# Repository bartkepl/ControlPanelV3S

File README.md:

# ControlPanelV3S — Hardware

KiCad project for the CAN-bus control panel board built around the Allwinner V3S (LicheePi Zero),
part of the [CANbusSensors](../) family of MPCC/MPSWP sensor-node projects. Two assembly variants
on one PCB: a handheld CAN-bus terminal and a VoIP endpoint. The next hardware iteration (Allwinner
T113-S3/4) will be a separate repo.

## Status: ready for prototype order

- Schematic and PCB layout done (4-layer, 120 × 75 mm), production files generated.
- Design review completed; DRC/ERC clean (remaining items reviewed and excluded as by-design).
- Hand assembly (2 fiducials on F.Cu for stencil alignment); crystal load caps C3/C4 are placeholders to be tuned at bring-up.

Production outputs: [schematic PDF](prod/sch/ControlPanel.pdf) · [PCB PDF](prod/pcb/ControlPanel.pdf) · [interactive BOM](prod/ibom/ControlPanel_ibom.html) · [gerbers](prod/ControlPanelV3S.zip)

## Renders

3D renders straight out of KiCad (`pcb/gen_media.kicad_jobset`), not photos — no boards have been
fabricated yet.

| Top | Bottom | Angle |
|---|---|---|
|  |  |  |

## Layout

- **`pcb/`** - KiCad project: CPU, power, CAN transceiver front-end, display/touch, GPS, Ethernet,
  audio.
- **`doc/`** - hardware design decisions and reference material. Start with
  [doc/README.md](doc/README.md), which says which document is the source of truth for what.
- **`media/`** - 3D renders of the board, generated from the KiCad project.
- **`prod/`** - fabrication outputs (gerber + drill zip, BOM, interactive BOM, schematic/PCB PDFs).

## Firmware

The firmware that runs on this board (V3S-side kiosk app, CAN-bus device monitor, offline
navigation/map stack) lives in a separate, currently private companion repo.

## License

MIT for original work - see [LICENSE](LICENSE). All footprints live under `pcb/local_lib/` and
were either authored locally or sourced from SamacSys (`BAT_MS621FE-FL11E.kicad_mod`); 
FunKey S is referenced in `doc/` as a comparison point for the Allwinner V3S reference design 
(e.g. power-tree, boot ROM behavior).

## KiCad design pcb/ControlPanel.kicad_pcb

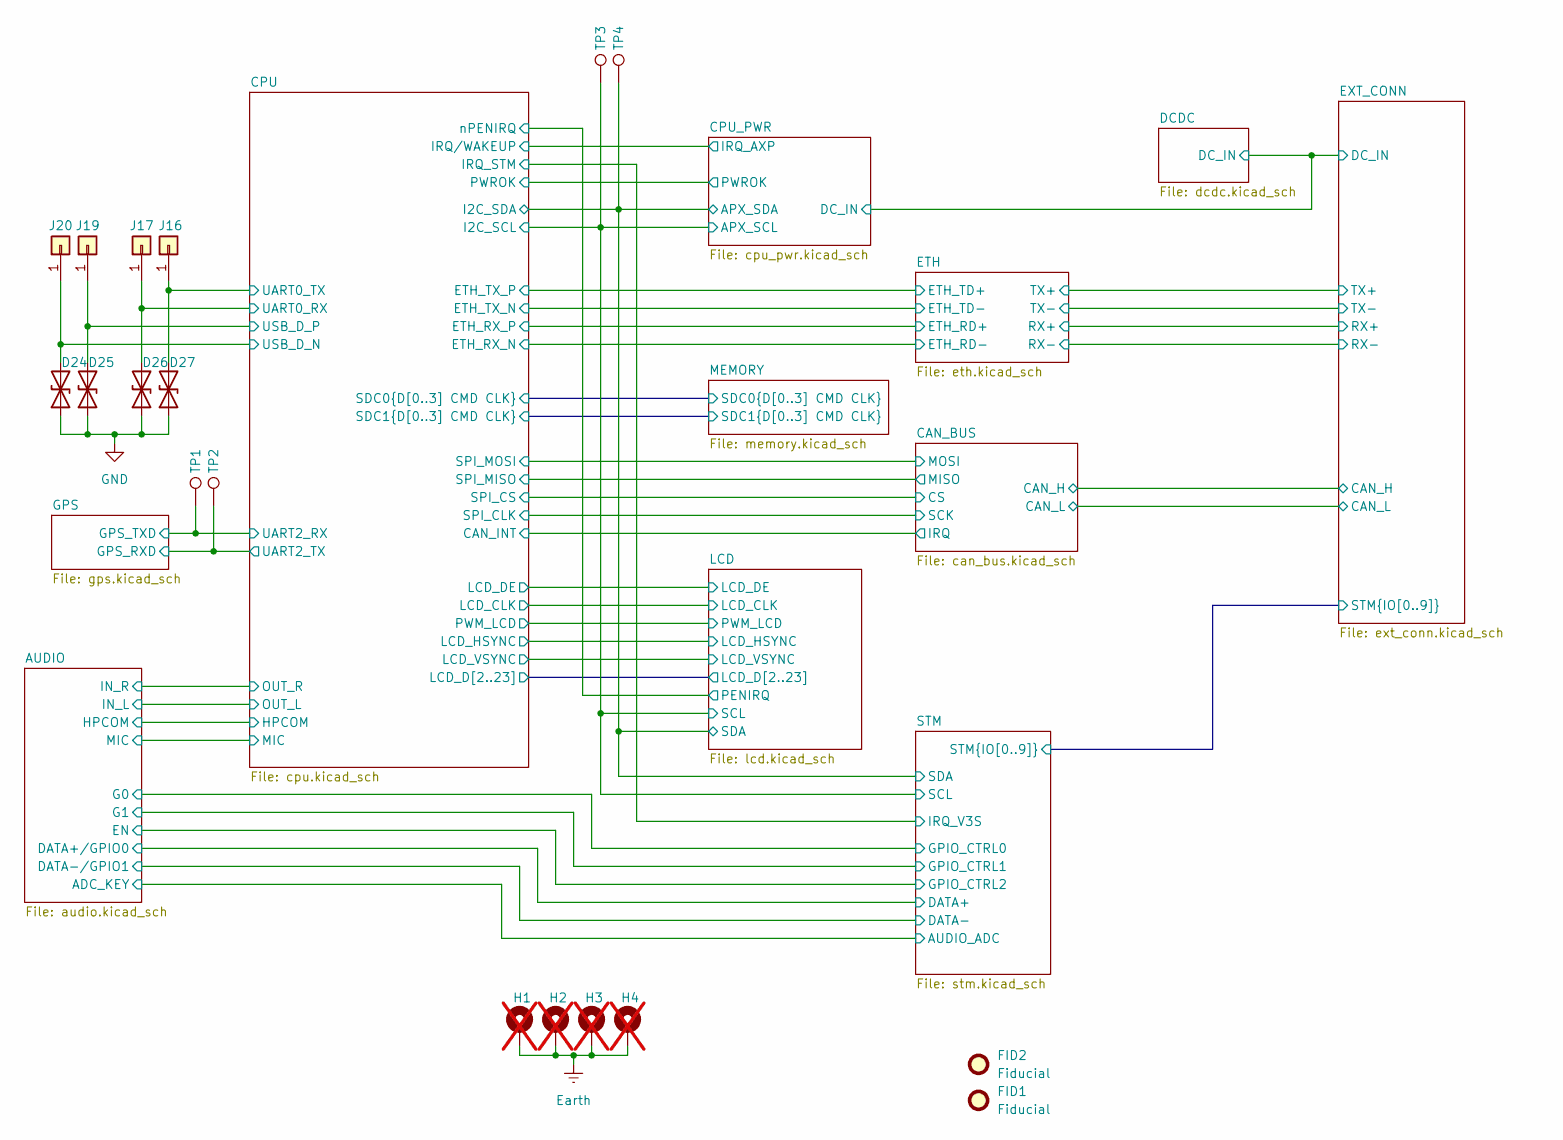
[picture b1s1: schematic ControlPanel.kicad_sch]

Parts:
D24, D25, D26, D27: STN061050BL40; D_0603_1608Metric; MPN STN061050BL40
FID1, FID2: Fiducial; Fiducial_0.5mm_Mask1mm
H1, H2, H3, H4: MountingHole_Pad; MountingHole_3.2mm_M3_ISO14580_Pad_TopBottom; not fitted
J16, J17, J19, J20: Conn_01x01; TestPoint_Pad_1.0x1.0mm
TP1, TP2, TP3, TP4: TestPoint; TestPoint_Pad_D1.0mm

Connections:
/CPU/I2C_SCL: TP3.1 (1_1); also elsewhere on the board
/CPU/I2C_SDA: TP4.1 (1_1); also elsewhere on the board
/CPU/UART0_RX: D26.2 (A2), J17.1 (Pin_1_1); also elsewhere on the board
/CPU/UART0_TX: D27.2 (A2), J16.1 (Pin_1_1); also elsewhere on the board
/CPU/UART2_RX: TP1.1 (1_1); also elsewhere on the board
/CPU/UART2_TX: TP2.1 (1_1); also elsewhere on the board
/CPU/USB_D_N: D24.2 (A2), J20.1 (Pin_1_1); also elsewhere on the board
/CPU/USB_D_P: D25.2 (A2), J19.1 (Pin_1_1); also elsewhere on the board
Earth: H1.1 (1_1), H2.1 (1_1), H3.1 (1_1), H4.1 (1_1); also elsewhere on the board
GND: D24.1 (A1), D25.1 (A1), D26.1 (A1), D27.1 (A1); also elsewhere on the board

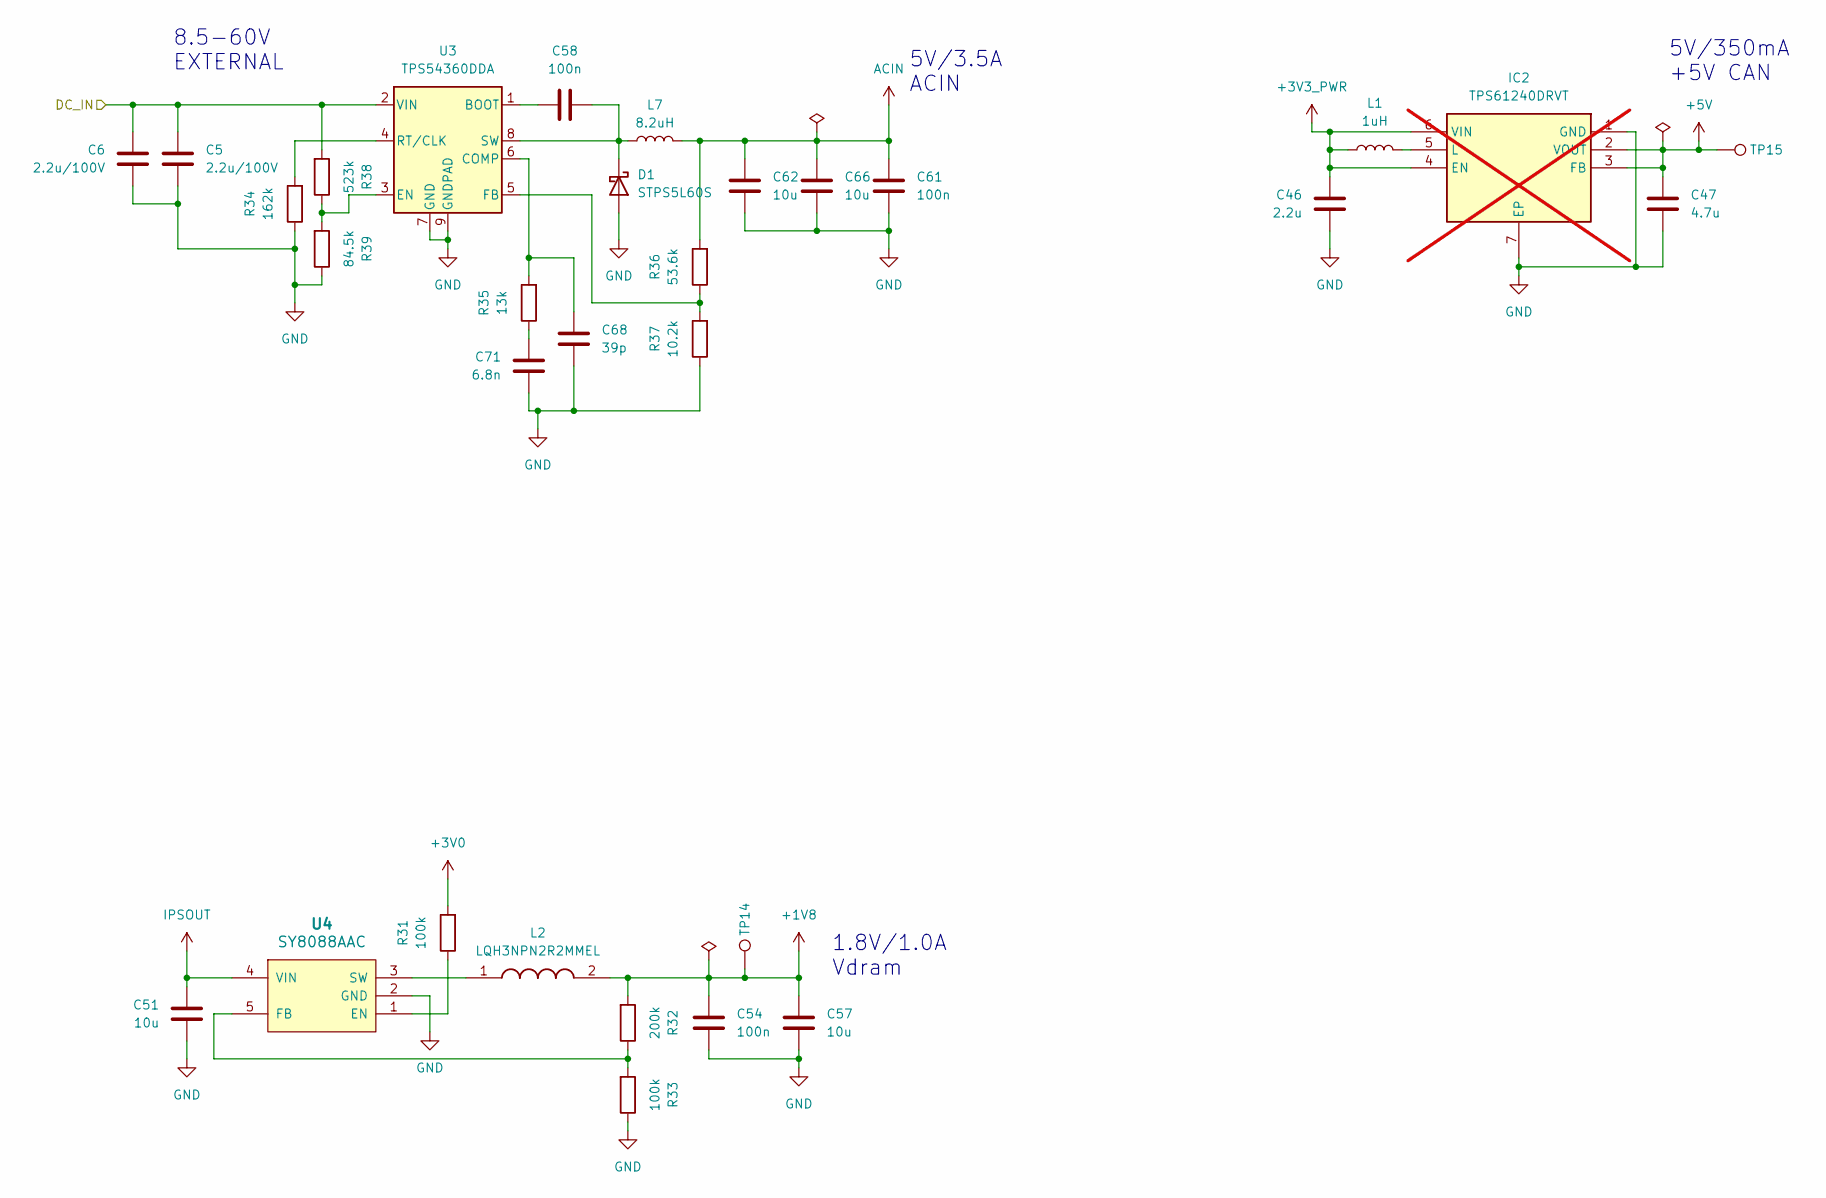
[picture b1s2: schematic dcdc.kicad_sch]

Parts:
C5, C6: 2.2u/100V; C_1206_3216Metric; MPN FS31X225K101EPG; LCSC C1021612
C46: 2.2u; C_0603_1608Metric; MPN GRM188R61H225KE11D; LCSC C162273
C47: 4.7u; C_0603_1608Metric; MPN CL10A475KL8NRNC; LCSC C307467
C51, C57, C62, C66: 10u; C_0603_1608Metric; MPN CL10A106MA8NRNC; LCSC C96446
C54, C58, C61: 100n; C_0603_1608Metric; MPN TCC0603X7R104K500CT; LCSC C282519
C68: 39p; C_0603_1608Metric; MPN TCC0603COG390J500CT; LCSC C376784
C71: 6.8n; C_0603_1608Metric; MPN C1608C0G1H682JT000N; LCSC C342851
D1: STPS5L60S; D_SMC; MPN STPS5L60S
IC2: TPS61240DRVT; SON65P200X200X80-7N; MPN TPS61240DRVR; LCSC C59567; not fitted
L1: 1uH; L_0603_1608Metric; MPN LQM18PH1R0MFRL
L2: LQH3NPN2R2MMEL; LQH3NPN100MMEL; MPN LQH3NPN2R2MMEL; Mouser 81-LQH3NPN2R2MMEL
L7: 8.2uH; HCM0703; MPN HCM0703-8R2-R
R31, R33: 100k; R_0603_1608Metric; MPN RC0603FR-07100KL; LCSC C14675
R32: 200k; R_0603_1608Metric; MPN CR0603F200KP05Z; LCSC C881057
R34: 162k; R_0603_1608Metric; MPN CQ03WAF1623T5E; LCSC C2770814
R35: 13k; R_0603_1608Metric; MPN CQ03WAF1302T5E; LCSC C2759758
R36: 53.6k; R_0603_1608Metric; MPN 0603WAF5362T5E; LCSC C23074
R37: 10.2k; R_0603_1608Metric; MPN RC0603FR-0710K2L; LCSC C183219
R38: 523k; R_0603_1608Metric; MPN RS-03K5233FT; LCSC C321936
R39: 84.5k; R_0603_1608Metric; MPN RS-03K8452FT; LCSC C322014
TP14, TP15: TestPoint; TestPoint_Pad_D1.0mm
U3: TPS54360DDA; TI_SO-PowerPAD-8_ThermalVias; MPN TPS54360DDAR; LCSC C44377
U4: SY8088AAC; SOT-23-5; MPN SY8088AAC; LCSC C79313

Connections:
+1V8: C54.1, C57.1, L2.2, R32.2, TP14.1 (1_1); also elsewhere on the board
+3V0: R31.2; also elsewhere on the board
+3V3_PWR: C46.2, IC2.4 (EN), IC2.6 (VIN), L1.2; also elsewhere on the board
+5V: C47.2, IC2.2 (VOUT), IC2.3 (FB), TP15.1 (1_1); also elsewhere on the board
/CPU_PWR/DC_IN: C5.1, C6.1, R38.2, U3.2 (VIN); also elsewhere on the board
ACIN: C61.1, C62.1, C66.1, L7.2, R36.2; also elsewhere on the board
GND: C5.2, C6.2, C46.1, C47.1, C51.2, C54.2, C57.2, C61.2, C62.2, C66.2, C68.2, C71.2, D1.2 (A), IC2.1 (GND), IC2.7 (EP), R33.1, R34.1, R37.1, R39.1, U3.7 (GND), U3.9 (GNDPAD), U4.2 (GND); also elsewhere on the board
IPSOUT: C51.1, U4.4 (VIN); also elsewhere on the board
unnamed: C71.1, R35.1
unnamed: C58.2, D1.1 (K), L7.1, U3.8 (SW)
unnamed: IC2.5 (L), L1.1
unnamed: C58.1, U3.1 (BOOT)
unnamed: C68.1, R35.2, U3.6 (COMP)
unnamed: R38.1, R39.2, U3.3 (EN)
unnamed: R36.1, R37.2, U3.5 (FB)
unnamed: R34.2, U3.4 (RT/CLK)
unnamed: R31.1, U4.1 (EN)
unnamed: R32.1, R33.2, U4.5 (FB)
unnamed: L2.1, U4.3 (SW)

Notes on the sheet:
8.5-60V EXTERNAL
5V/350mA +5V CAN
5V/3.5A ACIN
1.8V/1.0A Vdram

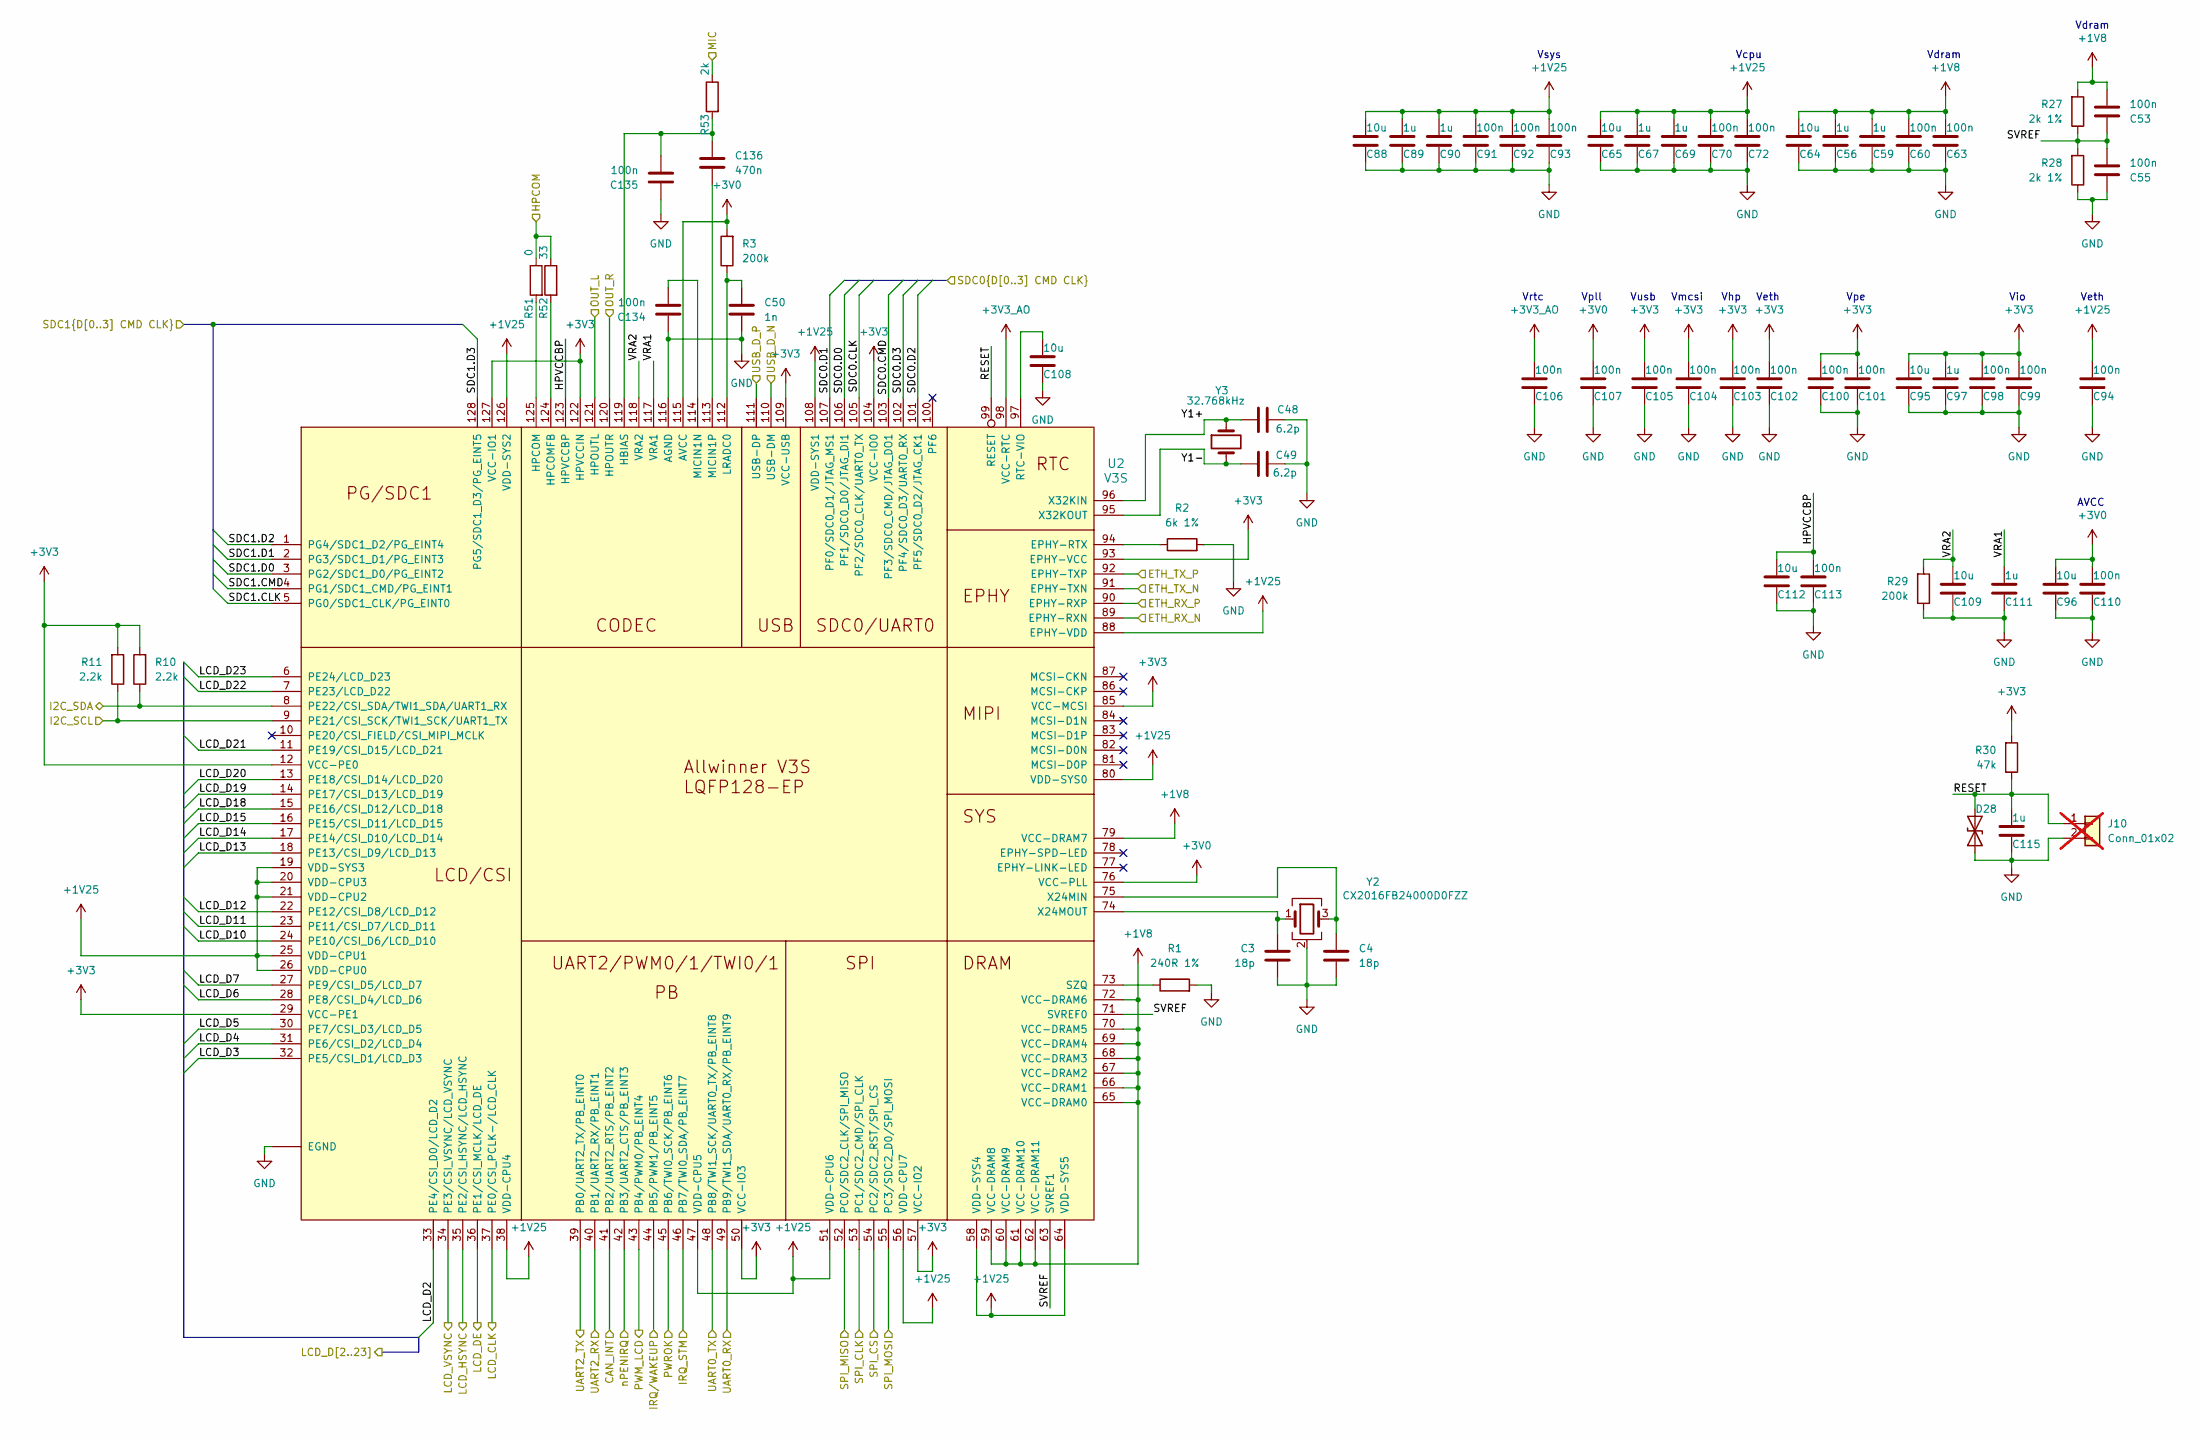
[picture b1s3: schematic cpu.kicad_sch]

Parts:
C3, C4: 18p; C_0402_1005Metric; MPN 0402CG180J500NT; LCSC C1549
C48, C49: 6.2p; C_0402_1005Metric; MPN CC0402CRNPO9BN6R2; LCSC C325456
C50: 1n; C_0603_1608Metric; MPN CC0603JRNPO9BN102; LCSC C106246
C53, C55, C60, C63, C70, C72, C91, C92, C93, C94, C98, C99, C100, C101, C102, C103, C104, C105, C106, C107, C110, C113, C134, C135: 100n; C_0603_1608Metric; MPN TCC0603X7R104K500CT; LCSC C282519
C56, C59, C67, C69, C89, C90, C97, C111, C115: 1u; C_0603_1608Metric; MPN 0603X105K500NT; LCSC C157684
C64, C65, C88, C95, C96, C108, C109, C112: 10u; C_0603_1608Metric; MPN CL10A106MA8NRNC; LCSC C96446
C136: 470n; C_0603_1608Metric; MPN CL10A474KB8NNNC; LCSC C170149
D28: STN061050BL40; D_0603_1608Metric; MPN STN061050BL40
J10: Conn_01x02; PinHeader_1x02_P1.00mm_Vertical; not fitted
R1: 240R 1%; R_0402_1005Metric; MPN 0402WGF2400TCE; LCSC C25094
R2: 6k 1%; R_0603_1608Metric; MPN RTT031202FTP; LCSC C103249
R3, R29: 200k; R_0603_1608Metric; MPN CR0603F200KP05Z; LCSC C881057
R10, R11: 2.2k; R_0603_1608Metric; MPN FRC0603F2201TS; LCSC C2907005
R27, R28: 2k 1%; R_0603_1608Metric; MPN RS-03K2001FT; LCSC C115336
R30: 47k; R_0603_1608Metric; MPN RTT034702FTP; LCSC C103657
R51: 0; R_0603_1608Metric; MPN 0603WAJ0000T5E; LCSC C15402
R52: 33; R_0603_1608Metric; MPN NQ03WAF330JT5E; LCSC C2780141
R53: 2k; R_0603_1608Metric; MPN RS-03K2001FT; LCSC C115336
U2: V3S; ELQFP-128; MPN V3s; LCSC C2687449
Y2: CX2016FB24000D0FZZ; Crystal_SMD_2016-4Pin_2.0x1.6mm; MPN CX2016FB24000D0FZZH1; LCSC C46629637
Y3: 32.768kHz; Crystal_SMD_MicroCrystal_CC7V-T1A-2Pin_3.2x1.5mm; MPN WTL1X80739BEL

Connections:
+1V8: C53.2, C56.2, C59.2, C60.2, C63.2, C64.2, R27.2, U2.59 (VCC-DRAM8), U2.60 (VCC-DRAM9), U2.61 (VCC-DRAM10), U2.62 (VCC-DRAM11), U2.65 (VCC-DRAM0), U2.66 (VCC-DRAM1), U2.67 (VCC-DRAM2), U2.68 (VCC-DRAM3), U2.69 (VCC-DRAM4), U2.70 (VCC-DRAM5), U2.72 (VCC-DRAM6), U2.79 (VCC-DRAM7); also elsewhere on the board
+1V25: C65.2, C67.2, C69.2, C70.2, C72.2, C88.2, C89.2, C90.2, C91.2, C92.2, C93.2, C94.2, U2.19 (VDD-SYS3), U2.20 (VDD-CPU3), U2.21 (VDD-CPU2), U2.25 (VDD-CPU1), U2.26 (VDD-CPU0), U2.38 (VDD-CPU4), U2.47 (VDD-CPU5), U2.51 (VDD-CPU6), U2.56 (VDD-CPU7), U2.58 (VDD-SYS4), U2.64 (VDD-SYS5), U2.80 (VDD-SYS0), U2.88 (EPHY-VDD), U2.108 (VDD-SYS1), U2.126 (VDD-SYS2); also elsewhere on the board
+3V0: C96.2, C107.2, C110.2, R3.2, U2.76 (VCC-PLL), U2.115 (AVCC); also elsewhere on the board
+3V3: C95.2, C97.2, C98.2, C99.2, C100.2, C101.2, C102.2, C103.2, C104.2, C105.2, R10.2, R11.2, R30.2, U2.12 (VCC-PE0), U2.29 (VCC-PE1), U2.50 (VCC-IO3), U2.57 (VCC-IO2), U2.85 (VCC-MCSI), U2.93 (EPHY-VCC), U2.104 (VCC-IO0), U2.109 (VCC-USB), U2.122 (HPVCCIN), U2.127 (VCC-IO1); also elsewhere on the board
+3V3_AO: C106.2, U2.98 (VCC-RTC); also elsewhere on the board
/AUDIO/HPCOM: R51.1, R52.1; also elsewhere on the board
/AUDIO/IN_L: U2.121 (HPOUTL); also elsewhere on the board
/AUDIO/IN_R: U2.120 (HPOUTR); also elsewhere on the board
/AUDIO/MIC: R53.1; also elsewhere on the board
/CAN_BUS/CS: U2.54 (PC2/SDC2_RST/SPI_CS); also elsewhere on the board
/CAN_BUS/IRQ: U2.41 (PB2/UART2_RTS/PB_EINT2); also elsewhere on the board
/CAN_BUS/MISO: U2.52 (PC0/SDC2_CLK/SPI_MISO); also elsewhere on the board
/CAN_BUS/MOSI: U2.55 (PC3/SDC2_D0/SPI_MOSI); also elsewhere on the board
/CAN_BUS/SCK: U2.53 (PC1/SDC2_CMD/SPI_CLK); also elsewhere on the board
/CPU/ETH_RX_N: U2.89 (EPHY-RXN); also elsewhere on the board
/CPU/ETH_RX_P: U2.90 (EPHY-RXP); also elsewhere on the board
/CPU/ETH_TX_N: U2.91 (EPHY-TXN); also elsewhere on the board
/CPU/ETH_TX_P: U2.92 (EPHY-TXP); also elsewhere on the board
/CPU/HPVCCBP: C112.2, C113.2, U2.123 (HPVCCBP)
/CPU/I2C_SCL: R11.1, U2.9 (PE21/CSI_SCK/TWI1_SCK/UART1_TX); also elsewhere on the board
/CPU/I2C_SDA: R10.1, U2.8 (PE22/CSI_SDA/TWI1_SDA/UART1_RX); also elsewhere on the board
/CPU/IRQ_STM: U2.46 (PB7/TWI0_SDA/PB_EINT7); also elsewhere on the board
/CPU/IRQ/WAKEUP: U2.44 (PB5/PWM1/PB_EINT5); also elsewhere on the board
/CPU/LCD_CLK: U2.37 (PE0/CSI_PCLK-/LCD_CLK); also elsewhere on the board
/CPU/LCD_D2: U2.33 (PE4/CSI_D0/LCD_D2); also elsewhere on the board
/CPU/LCD_D3: U2.32 (PE5/CSI_D1/LCD_D3); also elsewhere on the board
/CPU/LCD_D4: U2.31 (PE6/CSI_D2/LCD_D4); also elsewhere on the board
/CPU/LCD_D5: U2.30 (PE7/CSI_D3/LCD_D5); also elsewhere on the board
/CPU/LCD_D6: U2.28 (PE8/CSI_D4/LCD_D6); also elsewhere on the board
/CPU/LCD_D7: U2.27 (PE9/CSI_D5/LCD_D7); also elsewhere on the board
/CPU/LCD_D10: U2.24 (PE10/CSI_D6/LCD_D10); also elsewhere on the board
/CPU/LCD_D11: U2.23 (PE11/CSI_D7/LCD_D11); also elsewhere on the board
/CPU/LCD_D12: U2.22 (PE12/CSI_D8/LCD_D12); also elsewhere on the board
/CPU/LCD_D13: U2.18 (PE13/CSI_D9/LCD_D13); also elsewhere on the board
/CPU/LCD_D14: U2.17 (PE14/CSI_D10/LCD_D14); also elsewhere on the board
/CPU/LCD_D15: U2.16 (PE15/CSI_D11/LCD_D15); also elsewhere on the board
/CPU/LCD_D18: U2.15 (PE16/CSI_D12/LCD_D18); also elsewhere on the board
/CPU/LCD_D19: U2.14 (PE17/CSI_D13/LCD_D19); also elsewhere on the board
/CPU/LCD_D20: U2.13 (PE18/CSI_D14/LCD_D20); also elsewhere on the board
/CPU/LCD_D21: U2.11 (PE19/CSI_D15/LCD_D21); also elsewhere on the board
/CPU/LCD_D22: U2.7 (PE23/LCD_D22); also elsewhere on the board
/CPU/LCD_D23: U2.6 (PE24/LCD_D23); also elsewhere on the board
/CPU/LCD_DE: U2.36 (PE1/CSI_MCLK/LCD_DE); also elsewhere on the board
/CPU/LCD_HSYNC: U2.35 (PE2/CSI_HSYNC/LCD_HSYNC); also elsewhere on the board
/CPU/LCD_VSYNC: U2.34 (PE3/CSI_VSYNC/LCD_VSYNC); also elsewhere on the board
/CPU/PWM_LCD: U2.43 (PB4/PWM0/PB_EINT4); also elsewhere on the board
/CPU/PWROK: U2.45 (PB6/TWI0_SCK/PB_EINT6); also elsewhere on the board
/CPU/RESET: C115.2, D28.2 (A2), J10.1, R30.1, U2.99 (RESET)
/CPU/SDC0.CLK: U2.105 (PF2/SDC0_CLK/UART0_TX); also elsewhere on the board
/CPU/SDC0.CMD: U2.103 (PF3/SDC0_CMD/JTAG_DO1); also elsewhere on the board
/CPU/SDC0.D0: U2.106 (PF1/SDC0_D0/JTAG_DI1); also elsewhere on the board
/CPU/SDC0.D1: U2.107 (PF0/SDC0_D1/JTAG_MS1); also elsewhere on the board
/CPU/SDC0.D2: U2.101 (PF5/SDC0_D2/JTAG_CK1); also elsewhere on the board
/CPU/SDC0.D3: U2.102 (PF4/SDC0_D3/UART0_RX); also elsewhere on the board
/CPU/SDC1.CLK: U2.5 (PG0/SDC1_CLK/PG_EINT0); also elsewhere on the board
/CPU/SDC1.CMD: U2.4 (PG1/SDC1_CMD/PG_EINT1); also elsewhere on the board
/CPU/SDC1.D0: U2.3 (PG2/SDC1_D0/PG_EINT2); also elsewhere on the board
/CPU/SDC1.D1: U2.2 (PG3/SDC1_D1/PG_EINT3); also elsewhere on the board
/CPU/SDC1.D2: U2.1 (PG4/SDC1_D2/PG_EINT4); also elsewhere on the board
/CPU/SDC1.D3: U2.128 (PG5/SDC1_D3/PG_EINT5); also elsewhere on the board
/CPU/SVREF: C53.1, C55.2, R27.1, R28.2, U2.63 (SVREF1), U2.71 (SVREF0)
/CPU/UART0_RX: U2.49 (PB9/TWI1_SDA/UART0_RX/PB_EINT9); also elsewhere on the board
/CPU/UART0_TX: U2.48 (PB8/TWI1_SCK/UART0_TX/PB_EINT8); also elsewhere on the board
/CPU/UART2_RX: U2.40 (PB1/UART2_RX/PB_EINT1); also elsewhere on the board
/CPU/UART2_TX: U2.39 (PB0/UART2_TX/PB_EINT0); also elsewhere on the board
/CPU/USB_D_N: U2.110 (USB-DM); also elsewhere on the board
/CPU/USB_D_P: U2.111 (USB-DP); also elsewhere on the board
/CPU/VRA1: C111.2, U2.117 (VRA1)
/CPU/VRA2: C109.2, R29.2, U2.118 (VRA2)
/CPU/Y1+: C48.2, U2.96 (X32KIN), Y3.1
/CPU/Y1-: C49.2, U2.95 (X32KOUT), Y3.2
/CPU/nPENIRQ: U2.42 (PB3/UART2_CTS/PB_EINT3); also elsewhere on the board
GND: C3.2, C4.2, C48.1, C49.1, C50.2, C55.1, C56.1, C59.1, C60.1, C63.1, C64.1, C65.1, C67.1, C69.1, C70.1, C72.1, C88.1, C89.1, C90.1, C91.1, C92.1, C93.1, C94.1, C95.1, C96.1, C97.1, C98.1, C99.1, C100.1, C101.1, C102.1, C103.1, C104.1, C105.1, C106.1, C107.1, C108.1, C109.1, C110.1, C111.1, C112.1, C113.1, C115.1, C134.1, C135.1, D28.1 (A1), J10.2, R1.2, R2.2, R28.1, R29.1, U2.116 (AGND), U2.GND$1 (EGND), U2.GND$2 (EGND), U2.GND$3 (EGND), U2.GND$4 (EGND), U2.GND$5 (EGND), U2.GND$6 (EGND), U2.GND$7 (EGND), U2.GND$8 (EGND), U2.GND$9 (EGND), Y2.2 (G), Y2.4 (G); also elsewhere on the board
unnamed: R2.1, U2.94 (EPHY-RTX)
unnamed: C135.2, C136.2, R53.2, U2.119 (HBIAS)
unnamed: R51.2, U2.125 (HPCOM)
unnamed: R52.2, U2.124 (HPCOMFB)
unnamed: C50.1, R3.1, U2.112 (LRADC0)
unnamed: C134.2, U2.114 (MICIN1N)
unnamed: C136.1, U2.113 (MICIN1P)
unnamed: C108.2, U2.97 (RTC-VIO)
unnamed: R1.1, U2.73 (SZQ)
unnamed: C4.1, U2.75 (X24MIN), Y2.3
unnamed: C3.1, U2.74 (X24MOUT), Y2.1

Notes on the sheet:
AVCC
Vcpu
Vdram
Vusb
Vmcsi
Vrtc
Veth
Vpe
Vhp
Vio
Vpll
Vsys

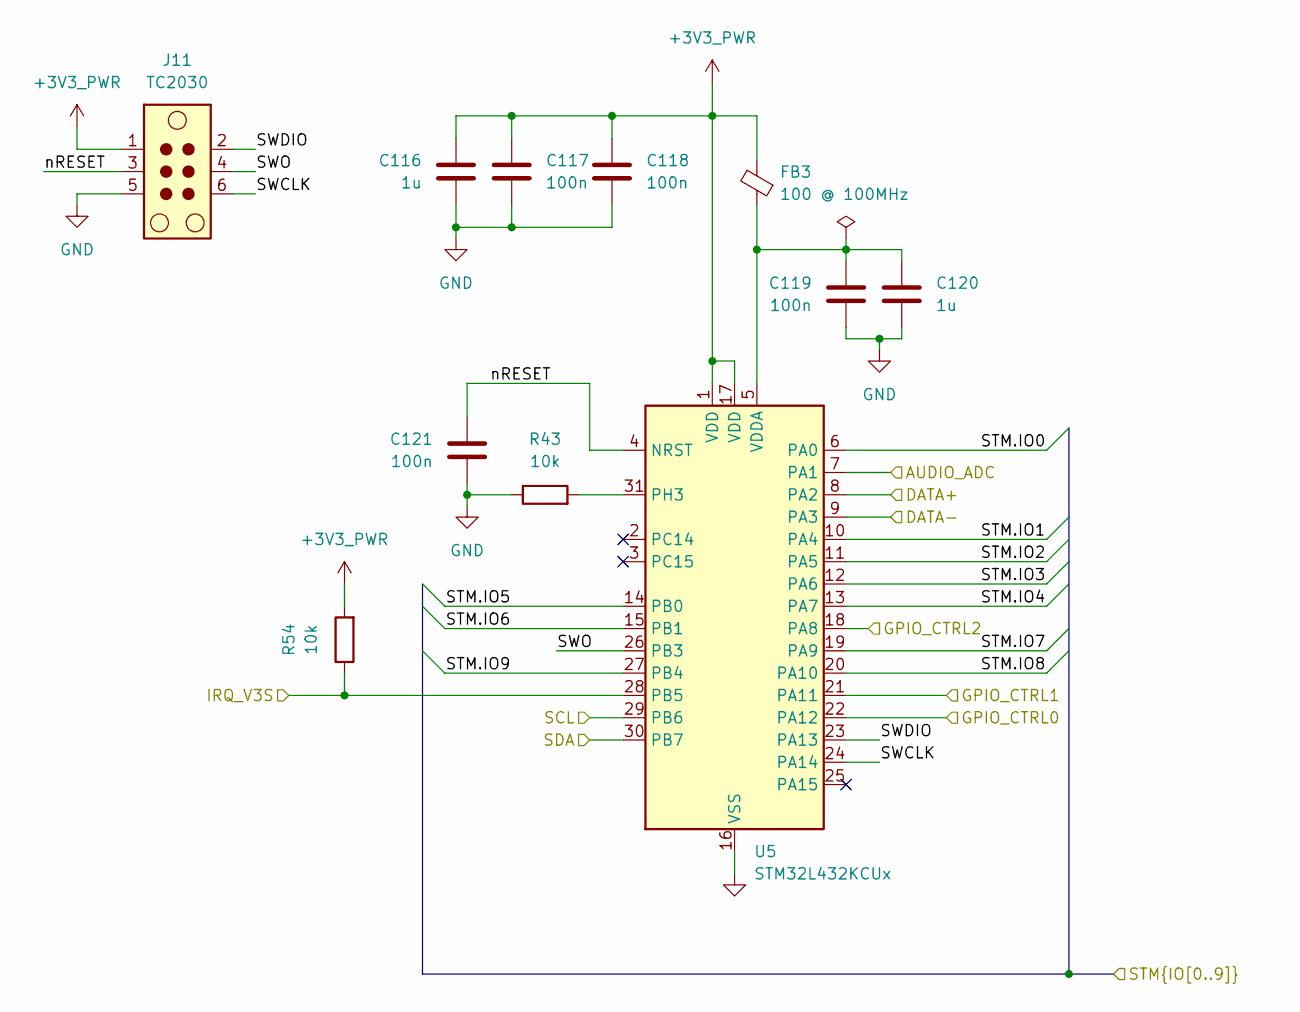
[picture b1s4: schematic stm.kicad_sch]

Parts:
C116, C120: 1u; C_0603_1608Metric; MPN 0603X105K500NT; LCSC C157684
C117, C118, C119, C121: 100n; C_0603_1608Metric; MPN TCC0603X7R104K500CT; LCSC C282519
FB3: 100 @ 100MHz; L_0603_1608Metric; MPN MH1608-101Y
J11: TC2030; Tag-Connect_TC2030-IDC-NL_2x03_P1.27mm_Vertical
R43, R54: 10k; R_0603_1608Metric; MPN RMS06FT1002; LCSC C209013
U5: STM32L432KCUx; QFN-32-1EP_5x5mm_P0.5mm_EP3.1x3.1mm; MPN STM32L432KCU6

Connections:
+3V3_PWR: C116.1, C117.2, C118.2, FB3.2, J11.1, R54.2, U5.1 (VDD), U5.17 (VDD); also elsewhere on the board
/AUDIO/ADC_KEY: U5.7 (PA1); also elsewhere on the board
/AUDIO/DATA+/GPIO0: U5.8 (PA2); also elsewhere on the board
/AUDIO/DATA-/GPIO1: U5.9 (PA3); also elsewhere on the board
/AUDIO/EN: U5.18 (PA8); also elsewhere on the board
/AUDIO/G0: U5.22 (PA12); also elsewhere on the board
/AUDIO/G1: U5.21 (PA11); also elsewhere on the board
/CPU/I2C_SCL: U5.29 (PB6); also elsewhere on the board
/CPU/I2C_SDA: U5.30 (PB7); also elsewhere on the board
/CPU/IRQ_STM: R54.1, U5.28 (PB5); also elsewhere on the board
/EXT_CONN/STM.IO0: U5.6 (PA0); also elsewhere on the board
/EXT_CONN/STM.IO1: U5.10 (PA4); also elsewhere on the board
/EXT_CONN/STM.IO2: U5.11 (PA5); also elsewhere on the board
/EXT_CONN/STM.IO3: U5.12 (PA6); also elsewhere on the board
/EXT_CONN/STM.IO4: U5.13 (PA7); also elsewhere on the board
/EXT_CONN/STM.IO5: U5.14 (PB0); also elsewhere on the board
/EXT_CONN/STM.IO6: U5.15 (PB1); also elsewhere on the board
/EXT_CONN/STM.IO7: U5.19 (PA9); also elsewhere on the board
/EXT_CONN/STM.IO8: U5.20 (PA10); also elsewhere on the board
/EXT_CONN/STM.IO9: U5.27 (PB4); also elsewhere on the board
/STM/SWCLK: J11.6, U5.24 (PA14)
/STM/SWDIO: J11.2, U5.23 (PA13)
/STM/SWO: J11.4, U5.26 (PB3)
/STM/nRESET: C121.2, J11.3, U5.4 (NRST)
GND: C116.2, C117.1, C118.1, C119.1, C120.2, C121.1, J11.5, R43.1, U5.16 (VSS), U5.32 (VSS), U5.33 (VSS); also elsewhere on the board
unnamed: R43.2, U5.31 (PH3)
unnamed: C119.2, C120.1, FB3.1, U5.5 (VDDA)

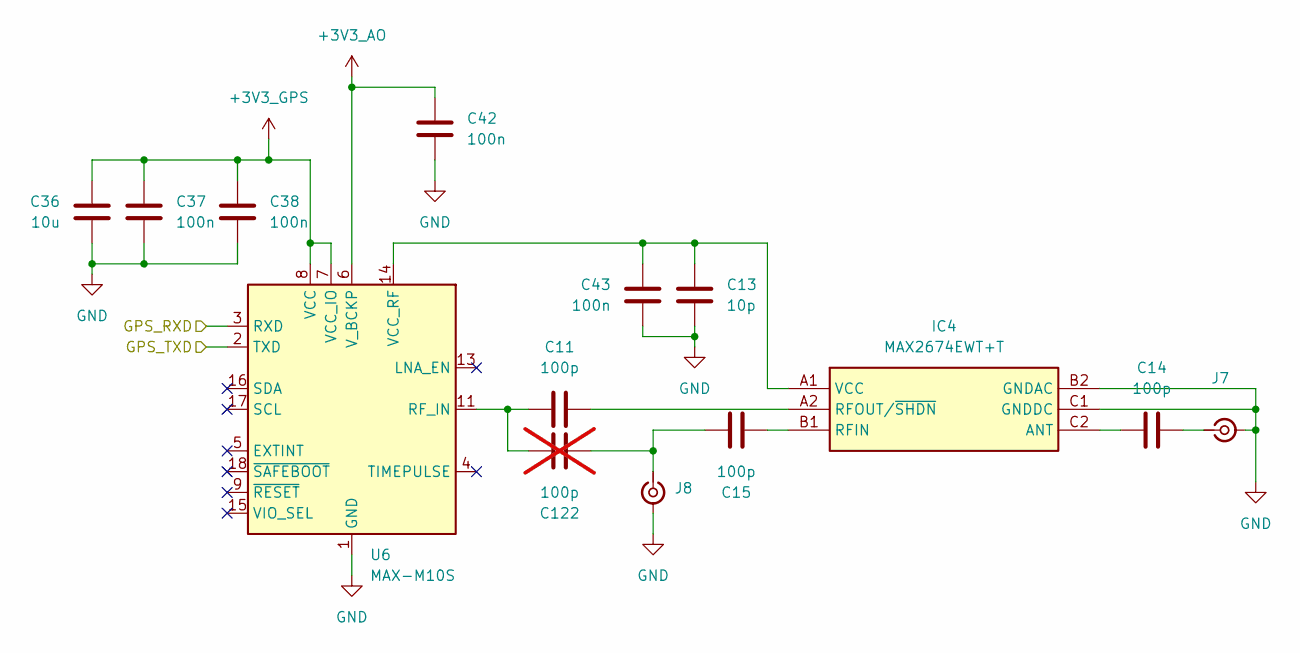
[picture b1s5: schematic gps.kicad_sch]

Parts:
C11, C14, C15: 100p; C_0402_1005Metric; MPN 0402N101G500CT; LCSC C387967
C13: 10p; C_0402_1005Metric; MPN 0402CG100D500NT; LCSC C313080
C36: 10u; C_0603_1608Metric; MPN CL10A106MA8NRNC; LCSC C96446
C37, C38, C42, C43: 100n; C_0603_1608Metric; MPN TCC0603X7R104K500CT; LCSC C282519
C122: 100p; C_0402_1005Metric; not fitted
IC4: MAX2674EWT+T; BGA6C40P2X3_83X123X69; MPN MAX2674EWT+T; Mouser 700-MAX2674EWT+T
J7, J8: Conn_Coaxial_Small; U.FL_Hirose_U.FL-R-SMT-1_Vertical; MPN U.FL-R-SMT-1(80); LCSC C88374
U6: MAX-M10S; ublox_MAX; MPN MAX-M10S-00B; LCSC C4153167

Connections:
+3V3_AO: C42.1, U6.6 (V_BCKP); also elsewhere on the board
+3V3_GPS: C36.1, C37.1, C38.1, U6.7 (VCC_IO), U6.8 (VCC); also elsewhere on the board
/CPU/UART2_RX: U6.2 (TXD); also elsewhere on the board
/CPU/UART2_TX: U6.3 (RXD); also elsewhere on the board
GND: C13.1, C36.2, C37.2, C38.2, C42.2, C43.2, IC4.B2 (GNDAC), IC4.C1 (GNDDC), J7.2 (Ext), J8.2 (Ext), U6.1 (GND), U6.10 (GND), U6.12 (GND); also elsewhere on the board
unnamed: C14.1, IC4.C2 (ANT)
unnamed: C15.2, IC4.B1 (RFIN)
unnamed: C11.2, IC4.A2 (RFOUT/~SHDN)
unnamed: C13.2, C43.1, IC4.A1 (VCC), U6.14 (VCC_RF)
unnamed: C14.2, J7.1 (In)
unnamed: C15.1, C122.2, J8.1 (In)
unnamed: C11.1, C122.1, U6.11 (RF_IN)

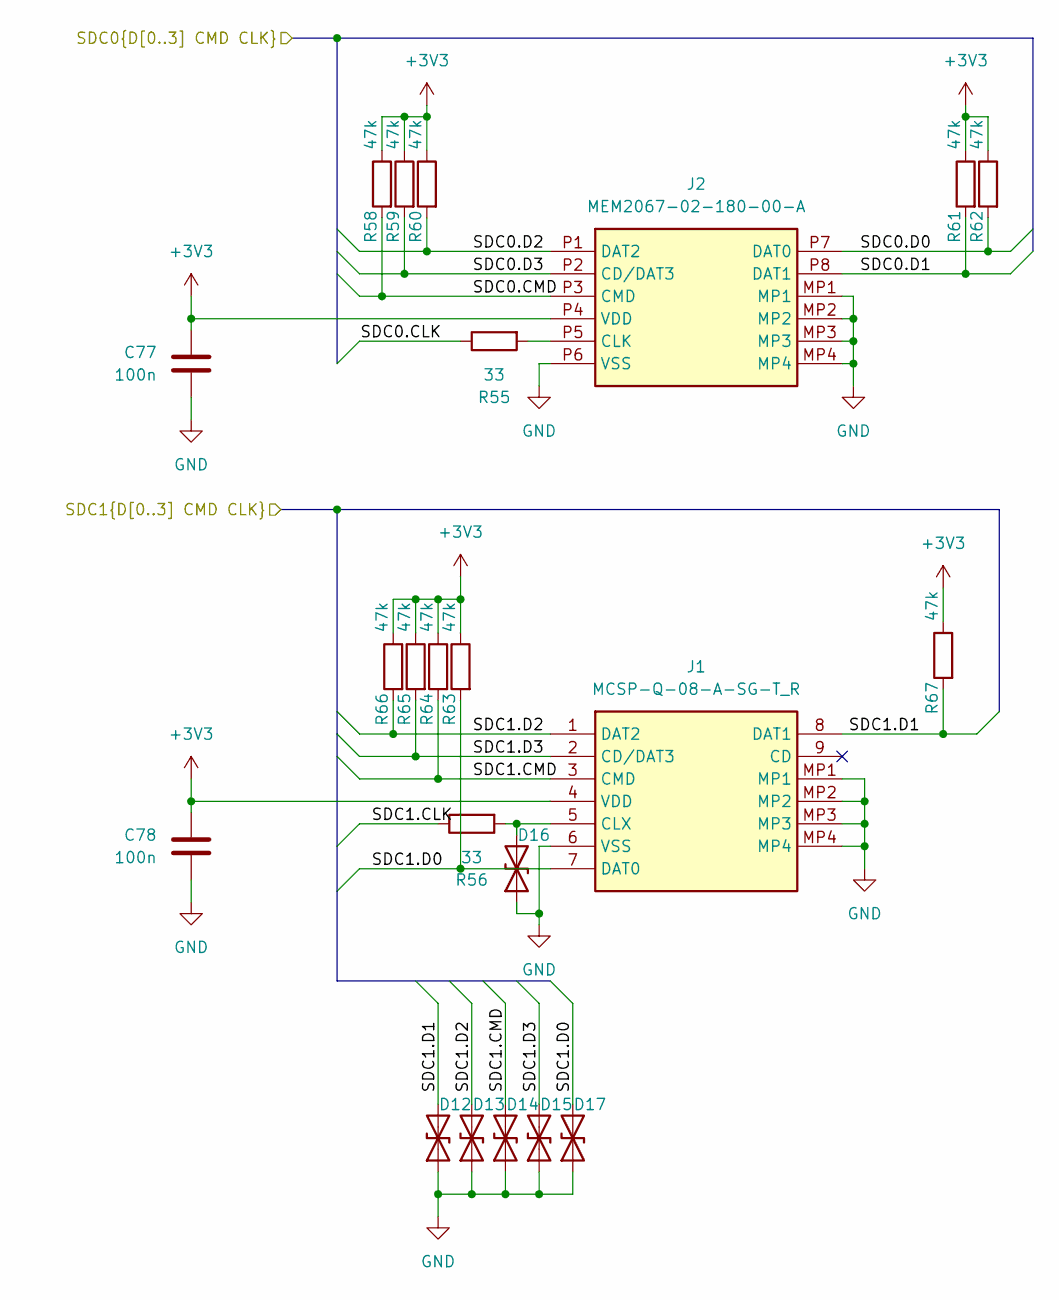
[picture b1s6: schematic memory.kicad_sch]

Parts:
C77, C78: 100n; C_0603_1608Metric; MPN TCC0603X7R104K500CT; LCSC C282519
D12, D13, D14, D15, D16, D17: STN061050BL40; D_0603_1608Metric; MPN STN061050BL40
J1: MCSP-Q-08-A-SG-T_R; MCSPQ08ASGTR; MPN 112J-TDAR-R01
J2: MEM2067-02-180-00-A; MEM20670218000A; MPN MEM2067-02-180-00-A; Mouser 640-MEM20670218000A
R55, R56: 33; R_0603_1608Metric; MPN NQ03WAF330JT5E; LCSC C2780141
R58, R59, R60, R61, R62, R63, R64, R65, R66, R67: 47k; R_0603_1608Metric; MPN RTT034702FTP; LCSC C103657

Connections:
+3V3: C77.2, C78.2, J1.4 (VDD), J2.P4 (VDD), R58.1, R59.1, R60.1, R61.1, R62.1, R63.1, R64.1, R65.1, R66.1, R67.1; also elsewhere on the board
/CPU/SDC0.CLK: R55.1; also elsewhere on the board
/CPU/SDC0.CMD: J2.P3 (CMD), R58.2; also elsewhere on the board
/CPU/SDC0.D0: J2.P7 (DAT0), R62.2; also elsewhere on the board
/CPU/SDC0.D1: J2.P8 (DAT1), R61.2; also elsewhere on the board
/CPU/SDC0.D2: J2.P1 (DAT2), R60.2; also elsewhere on the board
/CPU/SDC0.D3: J2.P2 (CD/DAT3), R59.2; also elsewhere on the board
/CPU/SDC1.CLK: R56.1; also elsewhere on the board
/CPU/SDC1.CMD: D14.2 (A2), J1.3 (CMD), R64.2; also elsewhere on the board
/CPU/SDC1.D0: D17.2 (A2), J1.7 (DAT0), R63.2; also elsewhere on the board
/CPU/SDC1.D1: D12.2 (A2), J1.8 (DAT1), R67.2; also elsewhere on the board
/CPU/SDC1.D2: D13.2 (A2), J1.1 (DAT2), R66.2; also elsewhere on the board
/CPU/SDC1.D3: D15.2 (A2), J1.2 (CD/DAT3), R65.2; also elsewhere on the board
GND: C77.1, C78.1, D12.1 (A1), D13.1 (A1), D14.1 (A1), D15.1 (A1), D16.1 (A1), D17.1 (A1), J1.6 (VSS), J1.MP1, J1.MP2, J1.MP3, J1.MP4, J2.MP1, J2.MP2, J2.MP3, J2.MP4, J2.P6 (VSS); also elsewhere on the board
unnamed: D16.2 (A2), J1.5 (CLX), R56.2
unnamed: J2.P5 (CLK), R55.2
